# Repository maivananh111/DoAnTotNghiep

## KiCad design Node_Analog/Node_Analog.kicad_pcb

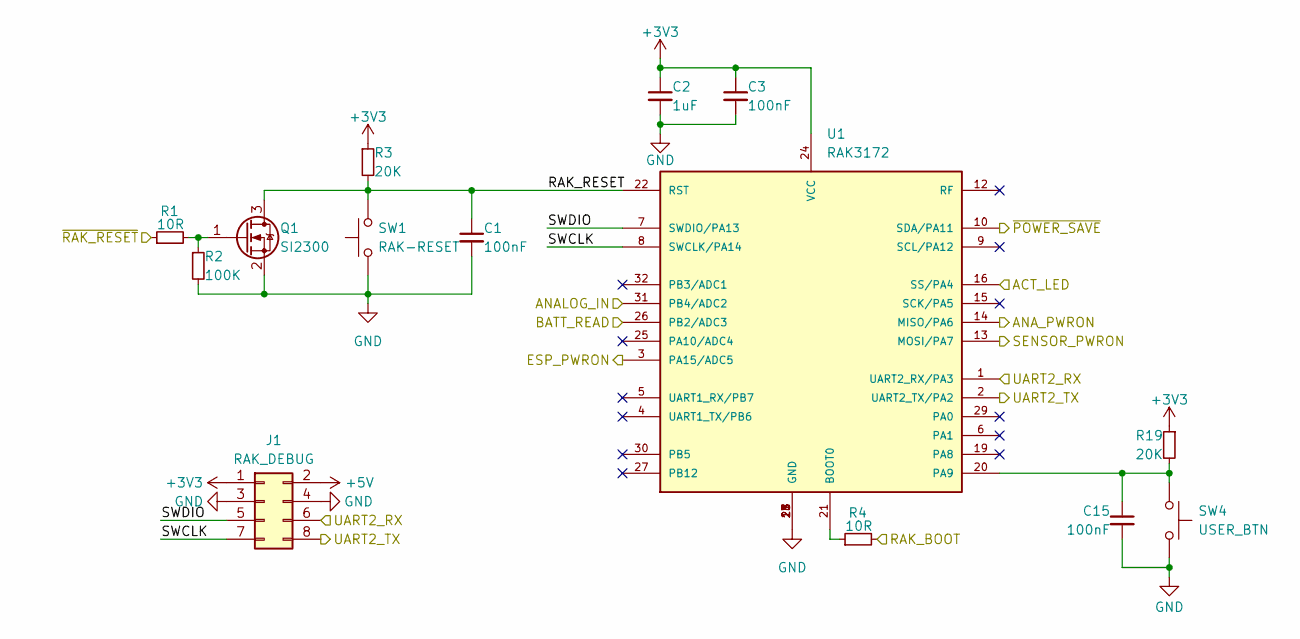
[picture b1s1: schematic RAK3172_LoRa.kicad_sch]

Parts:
C1, C3, C15: 100nF; C_0603
C2: 1uF; C_0603
J1: RAK_DEBUG; PinHeader_2x04_P2.54mm_Vertical
Q1: SI2300; SOT23-3
R1, R4: 10R; R_0603
R2: 100K; R_0603
R3, R19: 20K; R_0603
SW1: RAK-RESET; Switch_Tactile_6x6_Horizontal
SW4: USER_BTN; Switch_Tactile_6x6_Horizontal
U1: RAK3172

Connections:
+3V3: C2.1, C3.1, J1.1, R3.1, R19.1, U1.24 (VCC); also elsewhere on the board
+5V: J1.2; also elsewhere on the board
/Analog/ANALOG_OUT: U1.31 (PB4/ADC2); also elsewhere on the board
/ESP32-C3_BLE/ESP_PWRON: U1.3 (PA15/ADC5); also elsewhere on the board
/ESP32-C3_BLE/OTA_BOOT: R4.2; also elsewhere on the board
/ESP32-C3_BLE/OTA_RST: R1.1; also elsewhere on the board
/ESP32-C3_BLE/UART1_RX: J1.8, U1.2 (UART2_TX/PA2); also elsewhere on the board
/ESP32-C3_BLE/UART1_TX: J1.6, U1.1 (UART2_RX/PA3); also elsewhere on the board
/PSU/5V_EN: U1.13 (MOSI/PA7); also elsewhere on the board
/PSU/24V_EN: U1.14 (MISO/PA6); also elsewhere on the board
/PSU/ACT_LED: U1.16 (SS/PA4); also elsewhere on the board
/PSU/VBAT_MONITOR: U1.26 (PB2/ADC3); also elsewhere on the board
/PSU/~POWER_SAVE: U1.10 (SDA/PA11); also elsewhere on the board
/RAK3172_LoRa/RAK_RESET: C1.1, Q1.3 (D), R3.2, SW1.2, U1.22 (RST)
/RAK3172_LoRa/SWCLK: J1.7, U1.8 (SWCLK/PA14)
/RAK3172_LoRa/SWDIO: J1.5, U1.7 (SWDIO/PA13)
GND: C1.2, C2.2, C3.2, C15.2, J1.3, J1.4, Q1.2 (S), R2.2, SW1.1, SW4.1, U1.11 (GND), U1.17 (GND), U1.18 (GND), U1.23 (GND), U1.28 (GND); also elsewhere on the board
unnamed: Q1.1 (G), R1.2, R2.1
unnamed: R4.1, U1.21 (BOOT0)
unnamed: C15.1, R19.2, SW4.2, U1.20 (PA9)

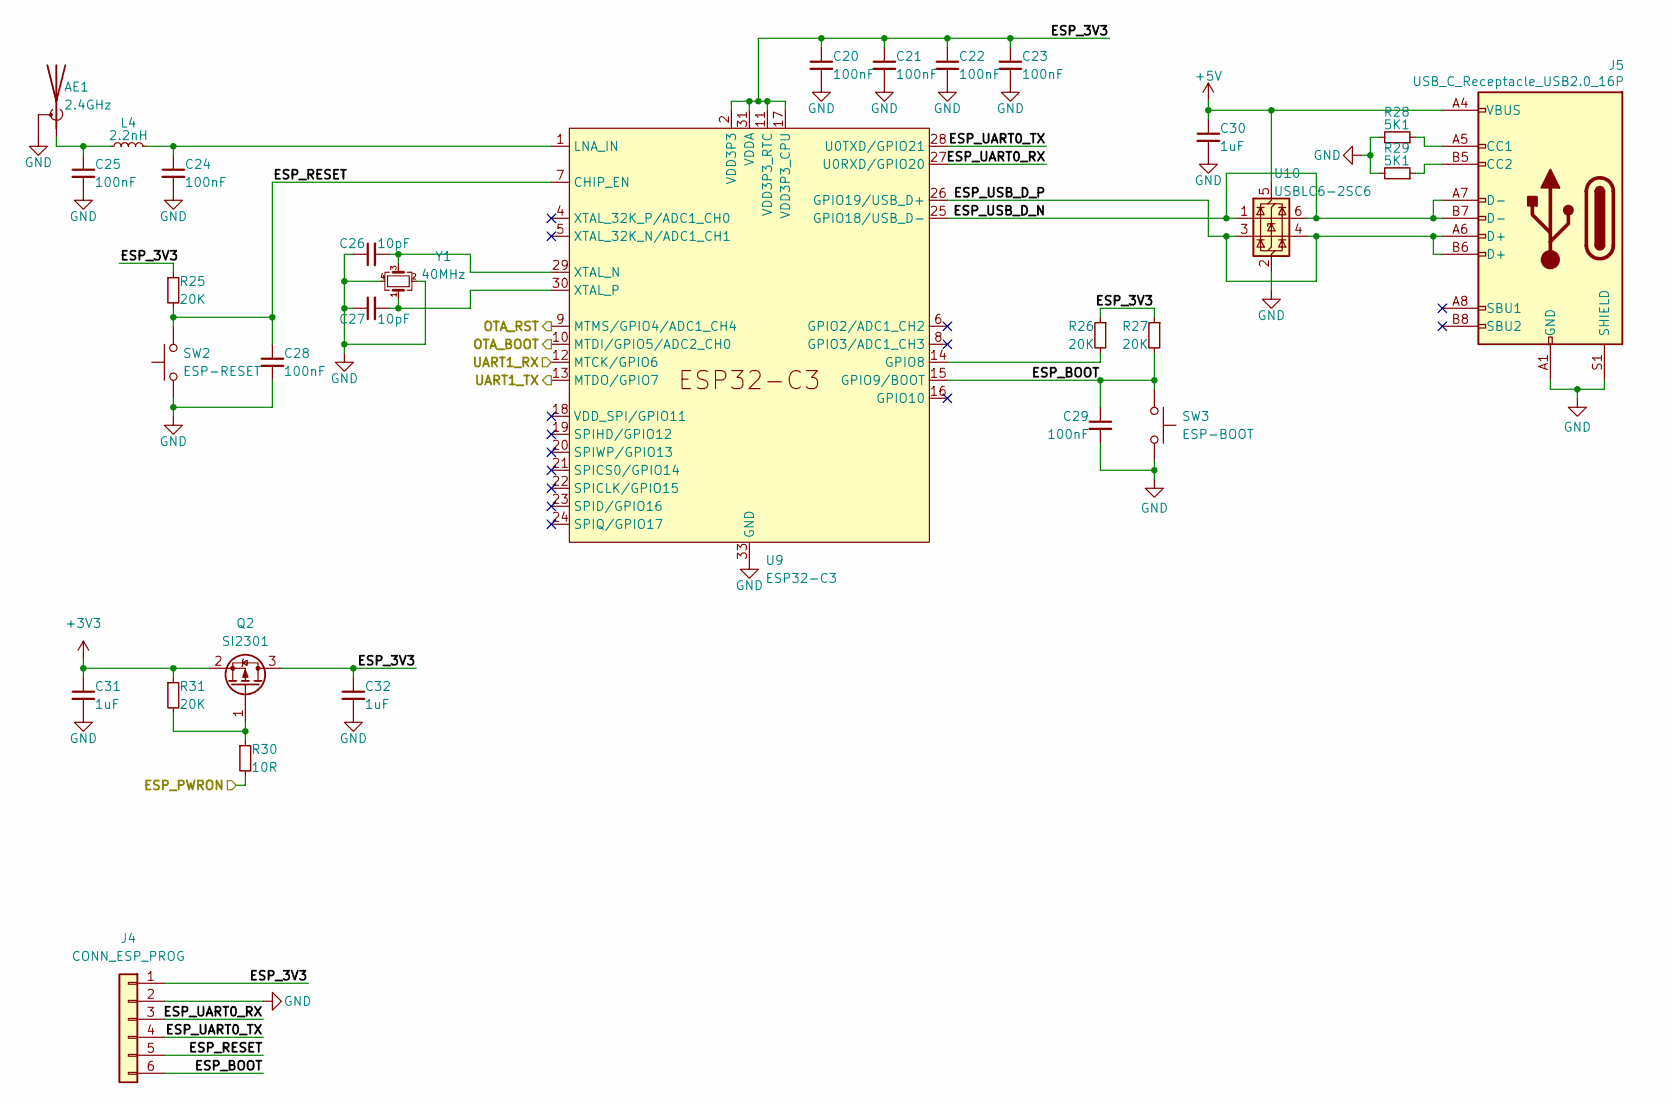
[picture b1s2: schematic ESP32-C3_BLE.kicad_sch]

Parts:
AE1: 2.4GHz; Texas_SWRA117D_2.4GHz_Right
C20, C21, C22, C23, C24, C25, C28, C29: 100nF; C_0603
C26, C27: 10pF; C_0603
C30, C31, C32: 1uF; C_0603
J4: CONN_ESP_PROG; XH_6P_2.54mm_Vertical
J5: USB_C_Receptacle_USB2.0_16P; USB-C_SMD_1
L4: 2.2nH; L_0603
Q2: SI2301; SOT23-3
R25, R26, R27, R31: 20K; R_0603
R28, R29: 5K1; R_0603
R30: 10R; R_0603
SW2: ESP-RESET; SW_SPST_CK
SW3: ESP-BOOT; SW_SPST_CK
U9: ESP32-C3; QFN-32_5x5_PAD-VIAS
U10: USBLC6-2SC6; SOT23-6
Y1: 40MHz; Crystal_3225_4P_1-4

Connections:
+3V3: C31.1, Q2.2 (S), R31.1; also elsewhere on the board
+5V: C30.1, J5.A4 (VBUS), J5.A9 (VBUS), J5.B4 (VBUS), J5.B9 (VBUS), U10.5 (VBUS); also elsewhere on the board
/ESP32-C3_BLE/ESP_3V3: C20.1, C21.1, C22.1, C23.1, C32.1, J4.1, Q2.3 (D), R25.1, R26.1, R27.1, U9.2 (VDD3P3), U9.3 (VDD3P3), U9.11 (VDD3P3_RTC), U9.17 (VDD3P3_CPU), U9.31 (VDDA), U9.32 (VDDA)
/ESP32-C3_BLE/ESP_BOOT: C29.1, J4.6, R27.2, SW3.2, U9.15 (GPIO9/BOOT)
/ESP32-C3_BLE/ESP_PWRON: R30.2; also elsewhere on the board
/ESP32-C3_BLE/ESP_RESET: C28.1, J4.5, R25.2, SW2.2, U9.7 (CHIP_EN)
/ESP32-C3_BLE/ESP_UART0_RX: J4.3, U9.27 (U0RXD/GPIO20)
/ESP32-C3_BLE/ESP_UART0_TX: J4.4, U9.28 (U0TXD/GPIO21)
/ESP32-C3_BLE/ESP_USB_D_N: J5.A7 (D-), J5.B7 (D-), U9.25 (GPIO18/USB_D-), U10.1 (I/O1), U10.6 (I/O1)
/ESP32-C3_BLE/ESP_USB_D_P: J5.A6 (D+), J5.B6 (D+), U9.26 (GPIO19/USB_D+), U10.3 (I/O2), U10.4 (I/O2)
/ESP32-C3_BLE/OTA_BOOT: U9.10 (MTDI/GPIO5/ADC2_CH0); also elsewhere on the board
/ESP32-C3_BLE/OTA_RST: U9.9 (MTMS/GPIO4/ADC1_CH4); also elsewhere on the board
/ESP32-C3_BLE/UART1_RX: U9.12 (MTCK/GPIO6); also elsewhere on the board
/ESP32-C3_BLE/UART1_TX: U9.13 (MTDO/GPIO7); also elsewhere on the board
GND: AE1.2 (Shield), C20.2, C21.2, C22.2, C23.2, C24.2, C25.2, C26.1, C27.1, C28.2, C29.2, C30.2, C31.2, C32.2, J4.2, J5.A1 (GND), J5.A12 (GND), J5.B1 (GND), J5.B12 (GND), J5.S1 (SHIELD), R28.2, R29.2, SW2.1, SW3.1, U9.33 (GND), U10.2 (GND), Y1.2, Y1.4; also elsewhere on the board
unnamed: AE1.1 (A), C25.1, L4.1
unnamed: J5.A5 (CC1), R28.1
unnamed: J5.B5 (CC2), R29.1
unnamed: Q2.1 (G), R30.1, R31.2
unnamed: R26.2, U9.14 (GPIO8)
unnamed: C24.1, L4.2, U9.1 (LNA_IN)
unnamed: C26.2, U9.29 (XTAL_N), Y1.3
unnamed: C27.2, U9.30 (XTAL_P), Y1.1

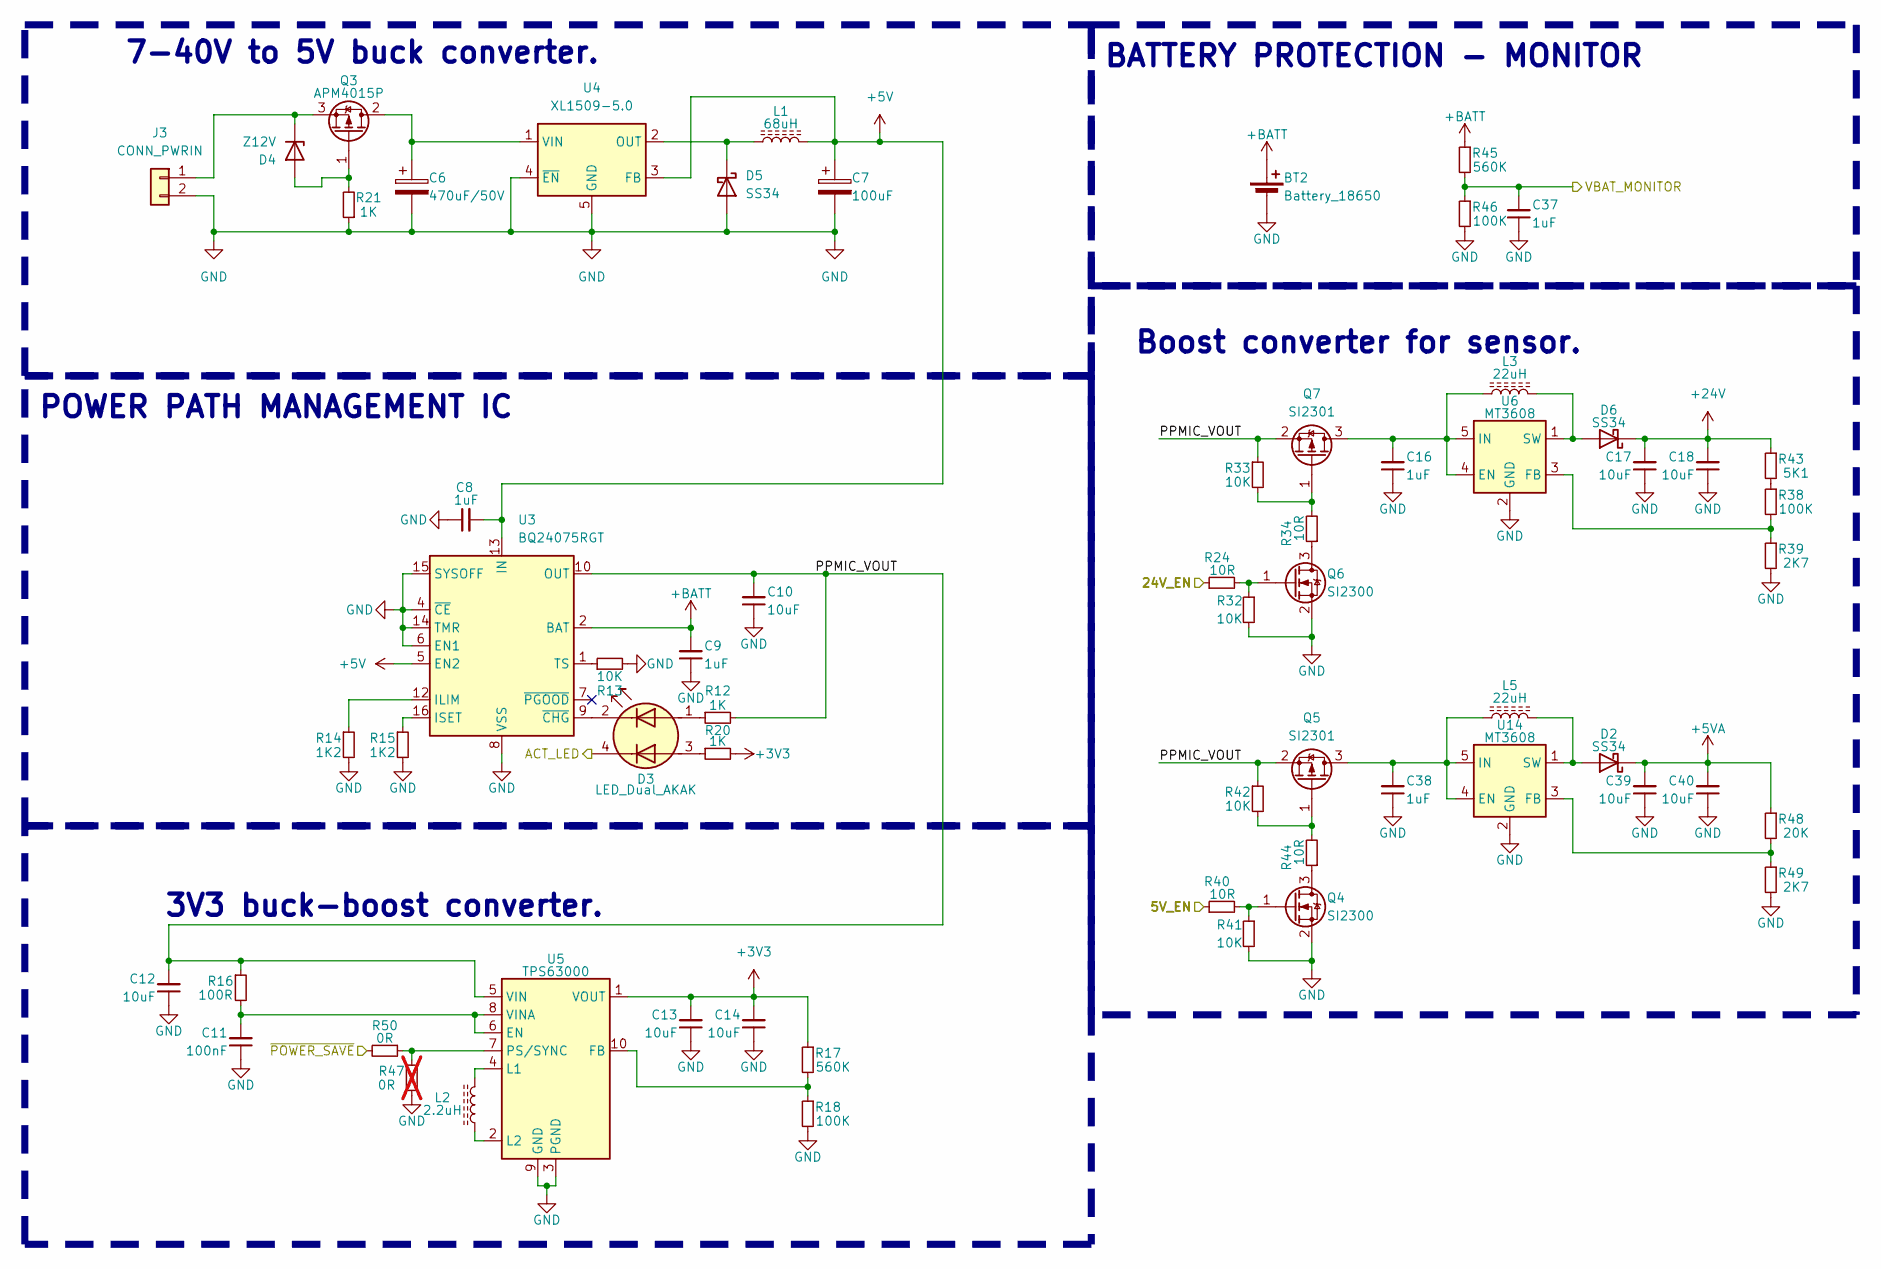
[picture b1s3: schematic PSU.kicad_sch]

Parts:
BT2: Battery_18650; XH_2P_2.54mm_Vertical
C6: 470uF/50V; CP_Elec_8x10.5
C7: 100uF; CP_Elec_6.3x7.7
C8, C9, C16, C37, C38: 1uF; C_0603
C10, C12, C13, C14, C17, C18, C39, C40: 10uF; C_0603
C11: 100nF; C_0603
D2, D5, D6: SS34; D_SMA
D3: LED_Dual_AKAK; LED_HOUSING_LH32K051F
D4: Z12V; D_MiniMELF
J3: CONN_PWRIN; PhoenixContact_MC_1,5_2-G-3.81_1x02_P3.81mm_Horizontal
L1: 68uH; L_12x12mm_H8mm
L2: 2.2uH; L_Bourns_SRN6045TA
L3, L5: 22uH; L_Bourns_SRN6045TA
Q3: APM4015P; TO-252-2
Q4, Q6: SI2300; SOT23-3
Q5, Q7: SI2301; SOT23-3
R12, R20, R21: 1K; R_0603
R13, R32, R33, R41, R42: 10K; R_0603
R14, R15: 1K2; R_0603
R16: 100R; R_0603
R17, R45: 560K; R_0603
R18, R38, R46: 100K; R_0603
R24, R34, R40, R44: 10R; R_0603
R39, R49: 2K7; R_0603
R43: 5K1; R_0603
R47: 0R; R_0603; not fitted
R48: 20K; R_0603
R50: 0R; R_0603
U3: BQ24075RGT; VQFN-16_3x3_PAD-VIAS
U4: XL1509-5.0; SOIC-8
U5: TPS63000; DRC-0010J
U6, U14: MT3608; SOT23-6

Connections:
+3V3: C13.2, C14.2, R17.1, R20.2, U5.1 (VOUT); also elsewhere on the board
+5V: C7.1, C8.2, L1.2, U3.5 (EN2), U3.13 (IN), U4.3 (FB); also elsewhere on the board
+5VA: C39.2, C40.2, D2.1 (K), R48.1; also elsewhere on the board
+24V: C17.2, C18.2, D6.1 (K), R43.1; also elsewhere on the board
+BATT: BT2.1 (+), C9.2, R45.1, U3.2 (BAT), U3.3 (BAT)
/PSU/5V_EN: R40.1; also elsewhere on the board
/PSU/24V_EN: R24.1; also elsewhere on the board
/PSU/ACT_LED: D3.4 (K2); also elsewhere on the board
/PSU/PPMIC_VOUT: C10.2, C12.2, Q5.2 (S), Q7.2 (S), R12.2, R16.1, R33.1, R42.1, U3.10 (OUT), U3.11 (OUT), U5.5 (VIN)
/PSU/VBAT_MONITOR: C37.2, R45.2, R46.1; also elsewhere on the board
/PSU/~POWER_SAVE: R50.2; also elsewhere on the board
GND: BT2.2 (-), C6.2, C7.2, C8.1, C9.1, C10.1, C11.1, C12.1, C13.1, C14.1, C16.1, C17.1, C18.1, C37.1, C38.1, C39.1, C40.1, D5.2 (A), J3.2, Q4.2 (S), Q6.2 (S), R13.2, R14.2, R15.2, R18.2, R21.1, R32.2, R39.2, R41.2, R46.2, R47.2, R49.2, U3.4 (~CE), U3.6 (EN1), U3.8 (VSS), U3.14 (TMR), U3.15 (SYSOFF), U3.17 (VSS), U4.4 (~EN), U4.5 (GND), U4.6 (GND), U4.7 (GND), U4.8 (GND), U5.3 (PGND), U5.9 (GND), U5.11 (PGND), U6.2 (GND), U14.2 (GND); also elsewhere on the board
unnamed: D2.2 (A), L5.2, U14.1 (SW)
unnamed: D3.1 (A1), R12.1
unnamed: D3.3 (A2), R20.1
unnamed: D3.2 (K1), U3.9 (~CHG)
unnamed: D4.2 (A), Q3.1 (G), R21.2
unnamed: D4.1 (K), J3.1, Q3.3 (S)
unnamed: D5.1 (K), L1.1, U4.2 (OUT)
unnamed: D6.2 (A), L3.2, U6.1 (SW)
unnamed: C6.1, Q3.2 (D), U4.1 (VIN)
unnamed: Q4.3 (D), R44.1
unnamed: Q4.1 (G), R40.2, R41.1
unnamed: C38.2, L5.1, Q5.3 (D), U14.4 (EN), U14.5 (IN)
unnamed: Q5.1 (G), R42.2, R44.2
unnamed: Q6.3 (D), R34.1
unnamed: Q6.1 (G), R24.2, R32.1
unnamed: C16.2, L3.1, Q7.3 (D), U6.4 (EN), U6.5 (IN)
unnamed: Q7.1 (G), R33.2, R34.2
unnamed: R38.1, R43.2
unnamed: R14.1, U3.12 (ILIM)
unnamed: R15.1, U3.16 (ISET)
unnamed: R13.1, U3.1 (TS)
unnamed: C11.2, R16.2, U5.6 (EN), U5.8 (VINA)
unnamed: R17.2, R18.1, U5.10 (FB)
unnamed: L2.2, U5.4 (L1)
unnamed: L2.1, U5.2 (L2)
unnamed: R47.1, R50.1, U5.7 (PS/SYNC)
unnamed: R38.2, R39.1, U6.3 (FB)
unnamed: R48.2, R49.1, U14.3 (FB)

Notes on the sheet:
3V3 buck-boost converter.
POWER PATH MANAGEMENT IC
BATTERY PROTECTION - MONITOR
7-40V to 5V buck converter.
Boost converter for sensor.

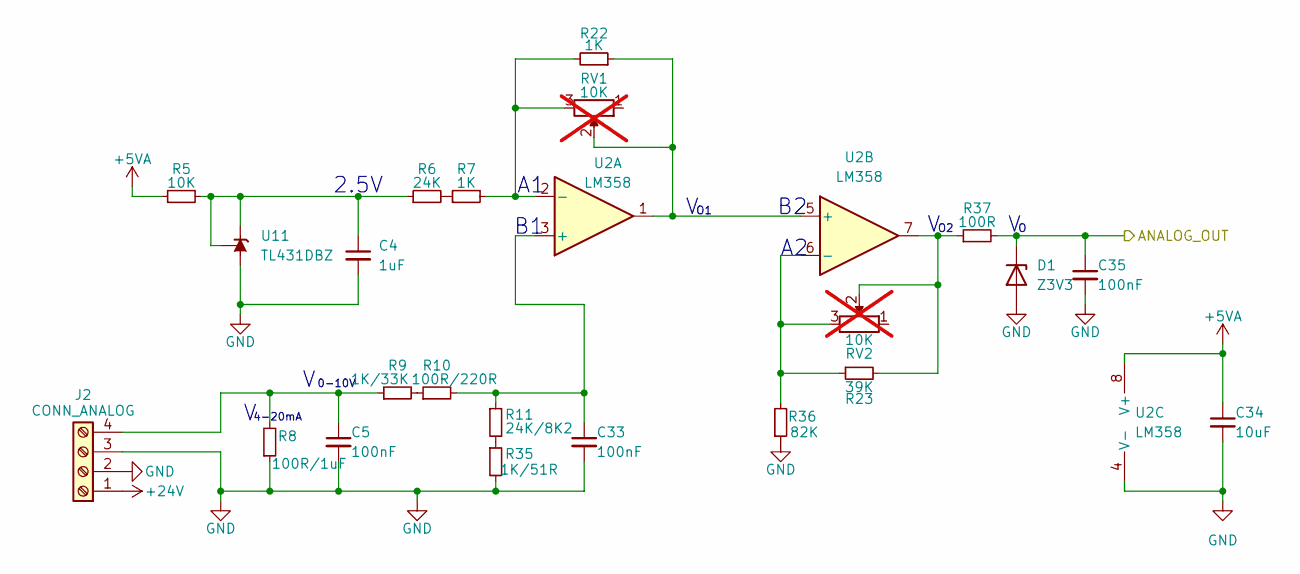
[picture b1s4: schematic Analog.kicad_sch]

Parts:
C4: 1uF; C_0603
C5, C33, C35: 100nF; C_0603
C34: 10uF; C_0603
D1: Z3V3; D_MiniMELF
J2: CONN_ANALOG; PhoenixContact_MC_1,5_4-G-3.81_1x04_P3.81mm_Horizontal
R5: 10K; R_0603
R6: 24K; R_0603
R7, R22: 1K; R_0603
R8: 100R/1uF; R_0805
R9: 1K/33K; R_0603
R10: 100R/220R; R_0603
R11: 24K/8K2; R_0603
R23: 39K; R_0603
R35: 1K/51R; R_0603
R36: 82K; R_0603
R37: 100R; R_0603
RV1, RV2: 10K; Potentiometer_Bourns_3296W_Vertical; not fitted
U2: LM358; SOIC-8
U11: TL431DBZ; SOT23-3

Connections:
+5VA: C34.1, R5.1, U2.8 (V+); also elsewhere on the board
+24V: J2.1; also elsewhere on the board
/Analog/ANALOG_OUT: C35.1, D1.1 (K), R37.2; also elsewhere on the board
GND: C4.2, C5.2, C33.2, C34.2, C35.2, D1.2 (A), J2.2, J2.3, R8.1, R35.2, R36.1, U2.4 (V-), U11.3 (A); also elsewhere on the board
unnamed: C5.1, J2.4, R8.2, R9.1
unnamed: R6.2, R7.1
unnamed: R9.2, R10.1
unnamed: R11.2, R35.1
unnamed: R23.2, R37.1, RV2.2, U2.7
unnamed: C33.1, R10.2, R11.1, U2.3 (+)
unnamed: R7.2, R22.2, RV1.3, U2.2 (-)
unnamed: R22.1, RV1.2, U2.1, U2.5 (+)
unnamed: R23.1, R36.2, RV2.3, U2.6 (-)
unnamed: C4.1, R5.2, R6.1, U11.1 (K), U11.2 (REF)

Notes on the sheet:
4-20mA
0-10V
2.5V

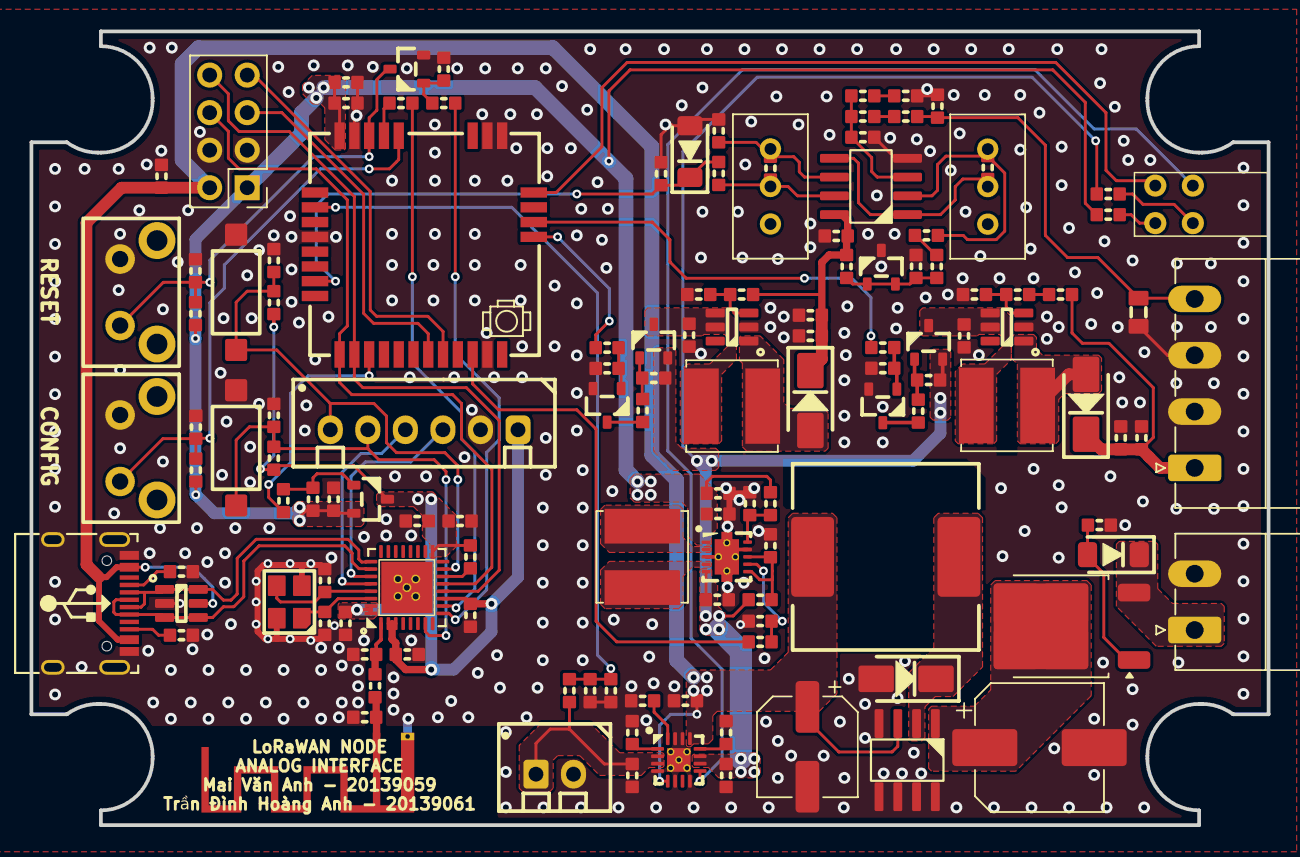
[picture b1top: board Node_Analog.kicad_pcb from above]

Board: 2 copper layers, 83.7 x 53.7 mm, 131 parts (1 on the bottom side), 77 nets.

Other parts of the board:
 : LOGO; LoGo_IoTVision_25x6.5

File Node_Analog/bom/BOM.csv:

null,References,Value,Footprint,Quantity,
1,"C1, C3, C5, C11, C15, C20, C21, C22, C23, C24, C25, C28, C29, C33, C35, C36",100nF,C_0603,16,
2,"C2, C4, C8, C9, C30, C31, C32, C37, C38",1uF,C_0603,9,
3,"C10, C12, C13, C14, C34, C39, C40",10uF,C_0603,7,
4,"C26, C27",10pF,C_0603,2,
5,C6,470uF/50V,CP_Elec_8x10.5,1,
6,C7,100uF,CP_Elec_6.3x7.7,1,
7,"R2, R3, R5, R13, R19, R25, R26, R27, R31, R41, R42",10K,R_0603,11,
8,"R1, R4, R30, R40, R44",10R,R_0603,5,
9,"R7, R12, R20, R21, R47",1K,R_0603,5,
10,"R16, R37, R43",100R,R_0603,3,
11,"R14, R15",1K2,R_0603,2,
12,"R17, R45",560K,R_0603,2,
13,"R18, R46",100K,R_0603,2,
14,"R28, R29",5K1,R_0603,2,
15,R6,24K,R_0603,1,https://www.thegioiic.com/dien-tro-24-kohm-0603-5-
16,R8,100R/DNP,R_0805,1,
17,R9,3K9/24K,R_0603,1,https://www.thegioiic.com/dien-tro-3-9-kohm-0603-5-
18,R10,100R/1K,R_0603,1,
19,R11,24K/10K,R_0603,1,
20,R35,100R/2K,R_0603,1,https://www.thegioiic.com/dien-tro-2-kohm-0603-1-
21,R36,8K2/DNP,R_0603,1,https://www.thegioiic.com/dien-tro-8-2-kohm-0603-1-
22,R48,20K,R_0603,1,
23,R49,2K7,R_0603,1,
24,L1,68uH,L_12x12mm_H8mm,1,
25,L2,2.2uH,L_Bourns_SRN6045TA,1,
26,L4,2.2nH,L_0603,1,
27,L5,22uH,L_Bourns_SRN6045TA,1,
28,"D2, D5",SS34,D_SMA,2,
29,D1,Z3V3,D_MiniMELF,1,https://www.thegioiic.com/zmm3v3-diode-zener-3-3v-500mw-smd
30,D3,LED_Dual_AKAK,LED_HOUSING_LH32K051F,1,
31,D4,Z12V,D_MiniMELF,1,
32,U1,RAK3172,RAK3172,1,
33,U2,LM358,SOIC-8,1,https://www.thegioiic.com/mcp6002-i-sn-ic-opamp-general-purp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
34,U3,BQ24075RGT,VQFN-16_3x3_PAD-VIAS,1,
35,U4,XL1509-5.0,SOIC-8,1,
36,U5,TPS63000,DRC-0010J,1,
37,U9,ESP32-C3,QFN-32_5x5_PAD-VIAS,1,
38,U10,USBLC6-2SC6,SOT23-6,1,
39,U11,TL431DBZ,SOT23-3,1,https://www.thegioiic.com/tl431-ic-tham-chieu-dien-ap-2-5-36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
40,U12,DW01A,SOT23-6,1,
41,U13,FS8205A,TSSOP-8_4.4x3mm_P0.65mm,1,
42,U14,MT3608,SOT23-6,1,
43,Y1,40MHz,Crystal_3225_4P_1-4,1,
44,SW1,RAK-RESET,Switch_Tactile_6x6_Horizontal,1,
45,SW2,ESP-RESET,SW_SPST_CK,1,
46,SW3,ESP-BOOT,SW_SPST_CK,1,
47,SW4,USER_BTN,Switch_Tactile_6x6_Horizontal,1,
48,"Q1, Q4",SI2300,SOT23-3,2,
49,"Q2, Q5",SI2301,SOT23-3,2,
50,"RV1, RV2",10K,Potentiometer_Bourns_3296W_Vertical,2,https://www.thegioiic.com/3296w-103-bien-tro-10-kohm-3-chan-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
51,AE1,2.4GHz,Texas_SWRA117D_2.4GHz_Right,1,
52,BT2,Battery_18650,XH_2P_2.54mm_Vertical,1,
53,Q3,APM4015P,TO-252-2,1,
54,J1,RAK_DEBUG,PinHeader_2x04_P2.54mm_Vertical,1,
55,J2,CONN_ANALOG,"PhoenixContact_MC_1,5_2-G-3.81_1x02_P3.81mm_Horizontal",1,
56,J3,CONN_PWRIN,"PhoenixContact_MC_1,5_2-G-3.81_1x02_P3.81mm_Horizontal",1,
57,J4,CONN_ESP_PROG,XH_6P_2.54mm_Vertical,1,
58,J5,USB_C_Receptacle_USB2.0_16P,USB-C_SMD_1,1,

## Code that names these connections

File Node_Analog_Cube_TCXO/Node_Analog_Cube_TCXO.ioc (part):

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Mcu.Name=STM32WLE5CCUx
Mcu.Package=UFQFPN48
Mcu.UserName=STM32WLE5CCUx
PA13.Mode=Serial_Wire
PA13.Signal=DEBUG_JTMS-SWDIO
PA14.Mode=Serial_Wire
PA14.Signal=DEBUG_JTCK-SWCLK
PA15.GPIOParameters=PinState,GPIO_Label
PA15.GPIO_Label=WF_PWR
PA15.PinState=GPIO_PIN_SET
PA15.Signal=GPIO_Output
PA2.GPIOParameters=GPIO_Speed,GPIO_PuPd
PA2.GPIO_PuPd=GPIO_PULLUP
PA2.GPIO_Speed=GPIO_SPEED_FREQ_VERY_HIGH
PA2.Mode=Asynchronous
PA2.Signal=LPUART1_TX
PA3.GPIOParameters=GPIO_Speed,GPIO_PuPd
PA3.GPIO_PuPd=GPIO_PULLUP
PA3.GPIO_Speed=GPIO_SPEED_FREQ_VERY_HIGH
PA3.Mode=Asynchronous
PA3.Signal=LPUART1_RX
PA4.GPIOParameters=GPIO_Label
PA4.GPIO_Label=LED_ACT
PA4.Signal=GPIO_Output
PA6.GPIOParameters=GPIO_Label
PA6.GPIO_Label=ANA_PWR
PA6.Signal=GPIO_Output
PA7.GPIOParameters=GPIO_Label
PA7.GPIO_Label=SENSOR_PWR
PA7.Signal=GPIO_Output
PA9.GPIOParameters=GPIO_Label,GPIO_ModeDefaultEXTI
PA9.GPIO_Label=CHMOD_BTN
PA9.GPIO_ModeDefaultEXTI=GPIO_MODE_IT_FALLING
PA9.Signal=GPXTI9
PB0-VDD_TCXO.Mode=HSE-TCXO
PB0-VDD_TCXO.Signal=VDDTCXO
PB2.GPIOParameters=GPIO_Label
PB2.GPIO_Label=VBAT
PB2.Mode=IN4
PB2.Signal=ADC_IN4
PB4.GPIOParameters=GPIO_Label
PB4.GPIO_Label=ANA
PB4.Mode=IN3
PB4.Signal=ADC_IN3
PB8.GPIOParameters=GPIO_Label
PB8.GPIO_Label=RF_CTRL1
PB8.Signal=GPIO_Output
PC13.GPIOParameters=GPIO_Label
PC13.GPIO_Label=RF_CTRL2
PC13.Signal=GPIO_Output
PC14-OSC32_IN.Mode=LSE-External-Oscillator
PC14-OSC32_IN.Signal=RCC_OSC32_IN
PC15-OSC32_OUT.Mode=LSE-External-Oscillator
PC15-OSC32_OUT.Signal=RCC_OSC32_OUT
RCC.HSE_VALUE=32000000
RCC.SYSCLKFreq_VALUE=48000000
board=custom

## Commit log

2024-05-21 Hardware bug pin PB12
2024-06-05 Tạm ổn
2024-06-06 change to state machine handler.
2024-06-06 New version.
2024-06-07 Fix bug viewdata không gửi lora được.
2024-06-27 Final.
